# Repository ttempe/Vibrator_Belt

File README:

Vibrator Belt. 
Copyright 2016, Thomas TEMPE

The purpose of this project is to build a (physical) vibrating belt as
a tool for sensory augmentation.  The belt is fitted with coin
vibrators along its length. The one that points north vibrates at all
time.  Use it continuously for 6 weeks, and you will grow a sense of
direction. Take it off, and you will experience amputation.

For more background (and an award-winning product that you can
actually buy), see http://www.feelspace.de/navibelt/

Directory contents:
Leather belt/		DXF files for manufacturing the flexible part 
			of the belt (fabric, foam, steel band...)
			Can be edited with LibreCAD.
Belt buckle/		Fusion360 model of the buckle (for aluminium 
     			machining or 3D printing)
Vibrator_Leather_Belt/	Kicad files for making the flexible electronic 
			circuit (along the length of the belt)
Vibrator_Leather_Belt_Control_Box/  Kicd files for making the PCB 
			circuit that fits in the buckle.
Photos/			Photos of prototypes.
Code/			Arduino code for the microcontroller.
Arduino/		Arduino hardware support for the microcontroller.

The control board uses an ATMega32u4 at 8MHz.
To get it running:
* Install the Arduino IDE from Arduino.cc. Run it once, then quit it.
* Copy Arduino/*/ into your Documents/Arduino directory
* solder an 8MHz external oscillator on the back of the control board
* Start the Arduino IDE. Select Tools->Board: -> Atmega32u4 on a breadboard (8MHz internal clock)
* Connect the ISP connector to an ISP programmer. Select the proper port in Tools->Port
* Click Tools->burn bootloader
* remove the external oscillator
* Tools->Board:->LilyPad Arduino USB
* File->Examples->01. Basics->Blink
* Click « Upload » on the icon bar. The « Signal » LED should blink with 0.5Hz frequency.
* open code/Compass_band5_leather/compass_band5_leather.ino in Arduino
* Click the « upload » icon on the icon bar. control code should be uploading.

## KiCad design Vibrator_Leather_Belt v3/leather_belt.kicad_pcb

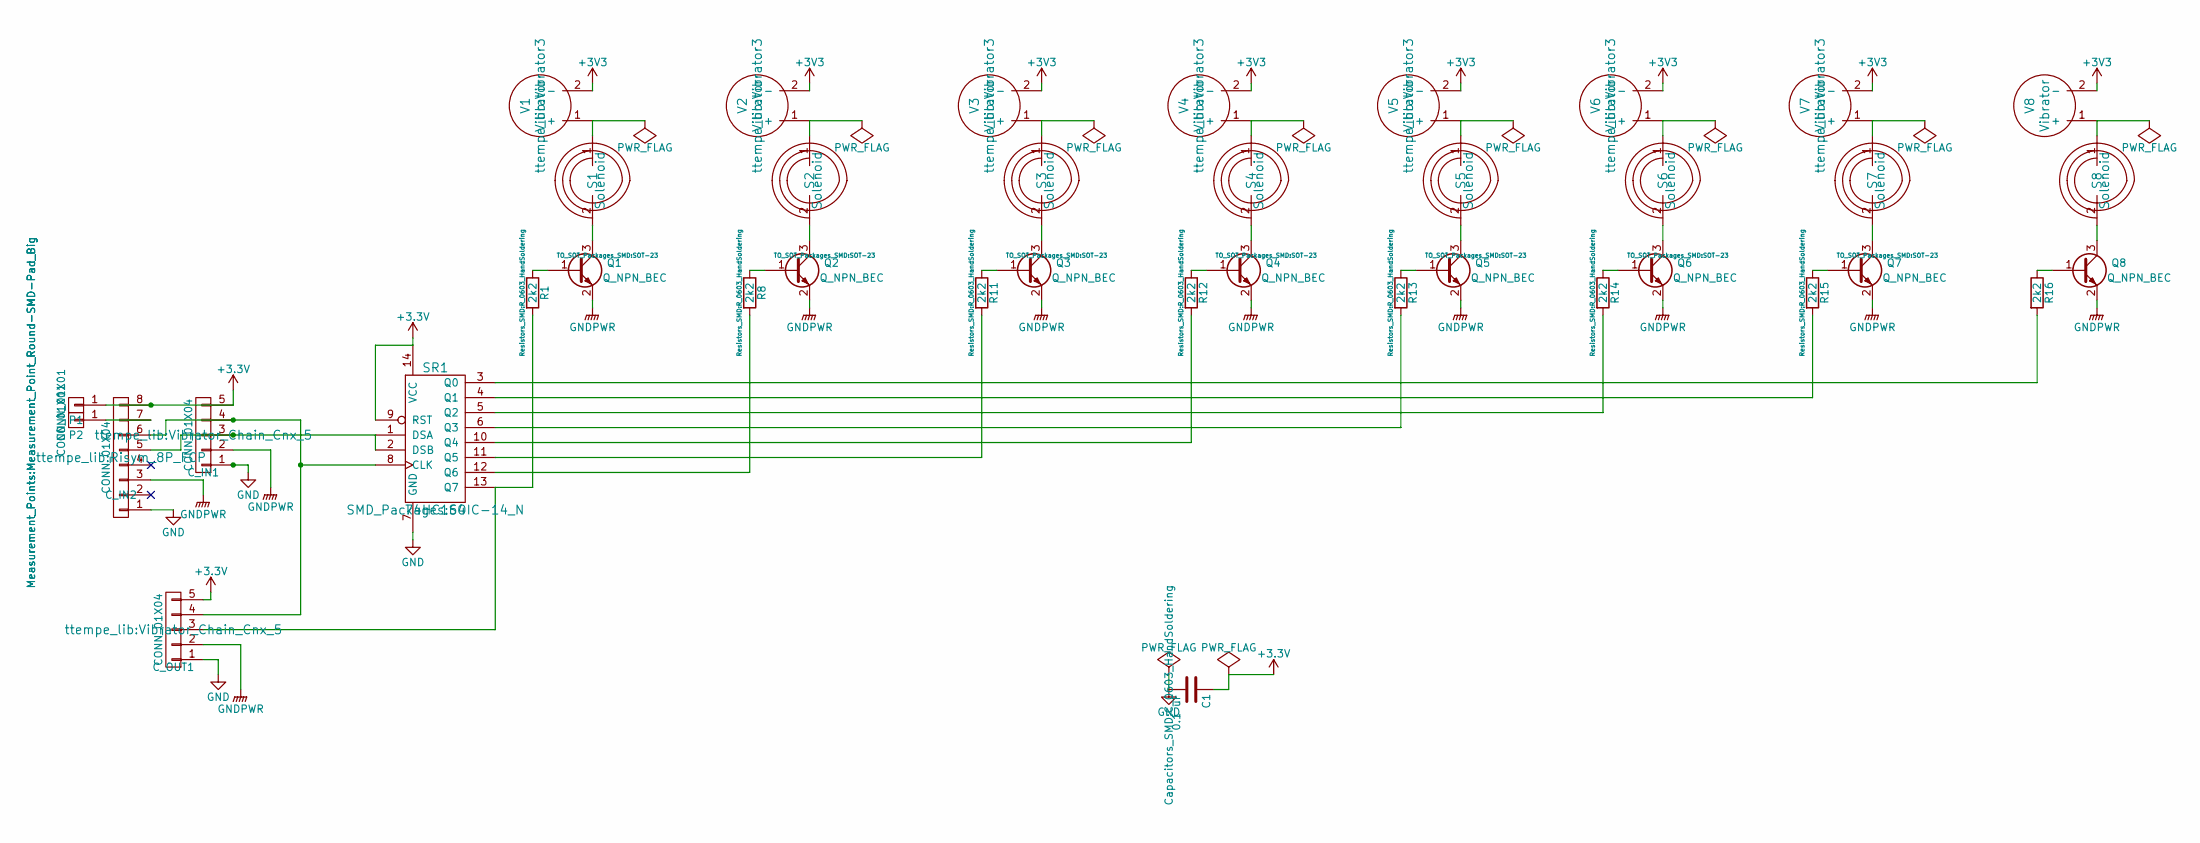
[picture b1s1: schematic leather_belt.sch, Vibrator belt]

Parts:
C1: 0.1 uF; C_0603_HandSoldering
C_IN1: CONN_01X04; Vibrator_Chain_Cnx_5
C_IN2: CONN_01X04; Risym_8P_FCP
C_OUT1: CONN_01X04; Vibrator_Chain_Cnx_5
P1, P2: CONN_01X01; Measurement_Point_Round-SMD-Pad_Big
Q1, Q2, Q3, Q4, Q5, Q6, Q7, Q8: Q_NPN_BEC; SOT-23
R1, R8, R11, R12, R13, R14, R15, R16: 2k2; R_0603_HandSoldering
S1, S2, S3, S4, S5, S6, S7, S8: Solenoid; Vibrator_antenna2
SR1: 74HC164; SOIC-14_N
V1, V2, V3, V4, V5, V6, V7, V8: Vibrator; Vibrator3

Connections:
GND: C1.2, C_IN1.1, C_IN2.1, C_OUT1.1, SR1.7 (GND)
GNDPWR: C_IN1.2, C_IN2.3, C_OUT1.2, Q1.2 (E), Q2.2 (E), Q3.2 (E), Q4.2 (E), Q5.2 (E), Q6.2 (E), Q7.2 (E), Q8.2 (E)
unnamed: C_IN1.3, C_IN2.5, SR1.1 (DSA), SR1.2 (DSB)
unnamed: C_IN1.4, C_IN2.6, C_OUT1.4, SR1.8 (CLK)
unnamed: C_IN2.7, P2.1
unnamed: C_OUT1.3, R1.2, SR1.13 (Q7)
unnamed: Q1.1 (B), R1.1
unnamed: Q1.3 (C), S1.2
unnamed: Q2.1 (B), R8.1
unnamed: Q2.3 (C), S2.2
unnamed: Q3.1 (B), R11.1
unnamed: Q3.3 (C), S3.2
unnamed: Q4.1 (B), R12.1
unnamed: Q4.3 (C), S4.2
unnamed: Q5.1 (B), R13.1
unnamed: Q5.3 (C), S5.2
unnamed: Q6.1 (B), R14.1
unnamed: Q6.3 (C), S6.2
unnamed: Q7.1 (B), R15.1
unnamed: Q7.3 (C), S7.2
unnamed: Q8.1 (B), R16.1
unnamed: Q8.3 (C), S8.2
unnamed: R8.2, SR1.12 (Q6)
unnamed: R11.2, SR1.11 (Q5)
unnamed: R12.2, SR1.10 (Q4)
unnamed: R13.2, SR1.6 (Q3)
unnamed: R14.2, SR1.5 (Q2)
unnamed: R15.2, SR1.4 (Q1)
unnamed: R16.2, SR1.3 (Q0)
unnamed: S1.1, V1.1 (+)
unnamed: S2.1, V2.1 (+)
unnamed: S3.1, V3.1 (+)
unnamed: S4.1, V4.1 (+)
unnamed: S5.1, V5.1 (+)
unnamed: S6.1, V6.1 (+)
unnamed: S7.1, V7.1 (+)
unnamed: S8.1, V8.1 (+)

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
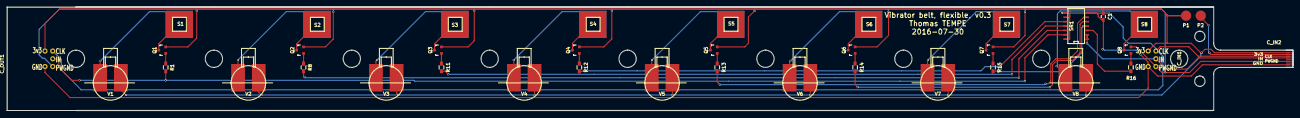
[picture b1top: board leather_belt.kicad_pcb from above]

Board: 2 copper layers, 373.0 x 30.0 mm, 39 parts (0 on the bottom side), 38 nets.

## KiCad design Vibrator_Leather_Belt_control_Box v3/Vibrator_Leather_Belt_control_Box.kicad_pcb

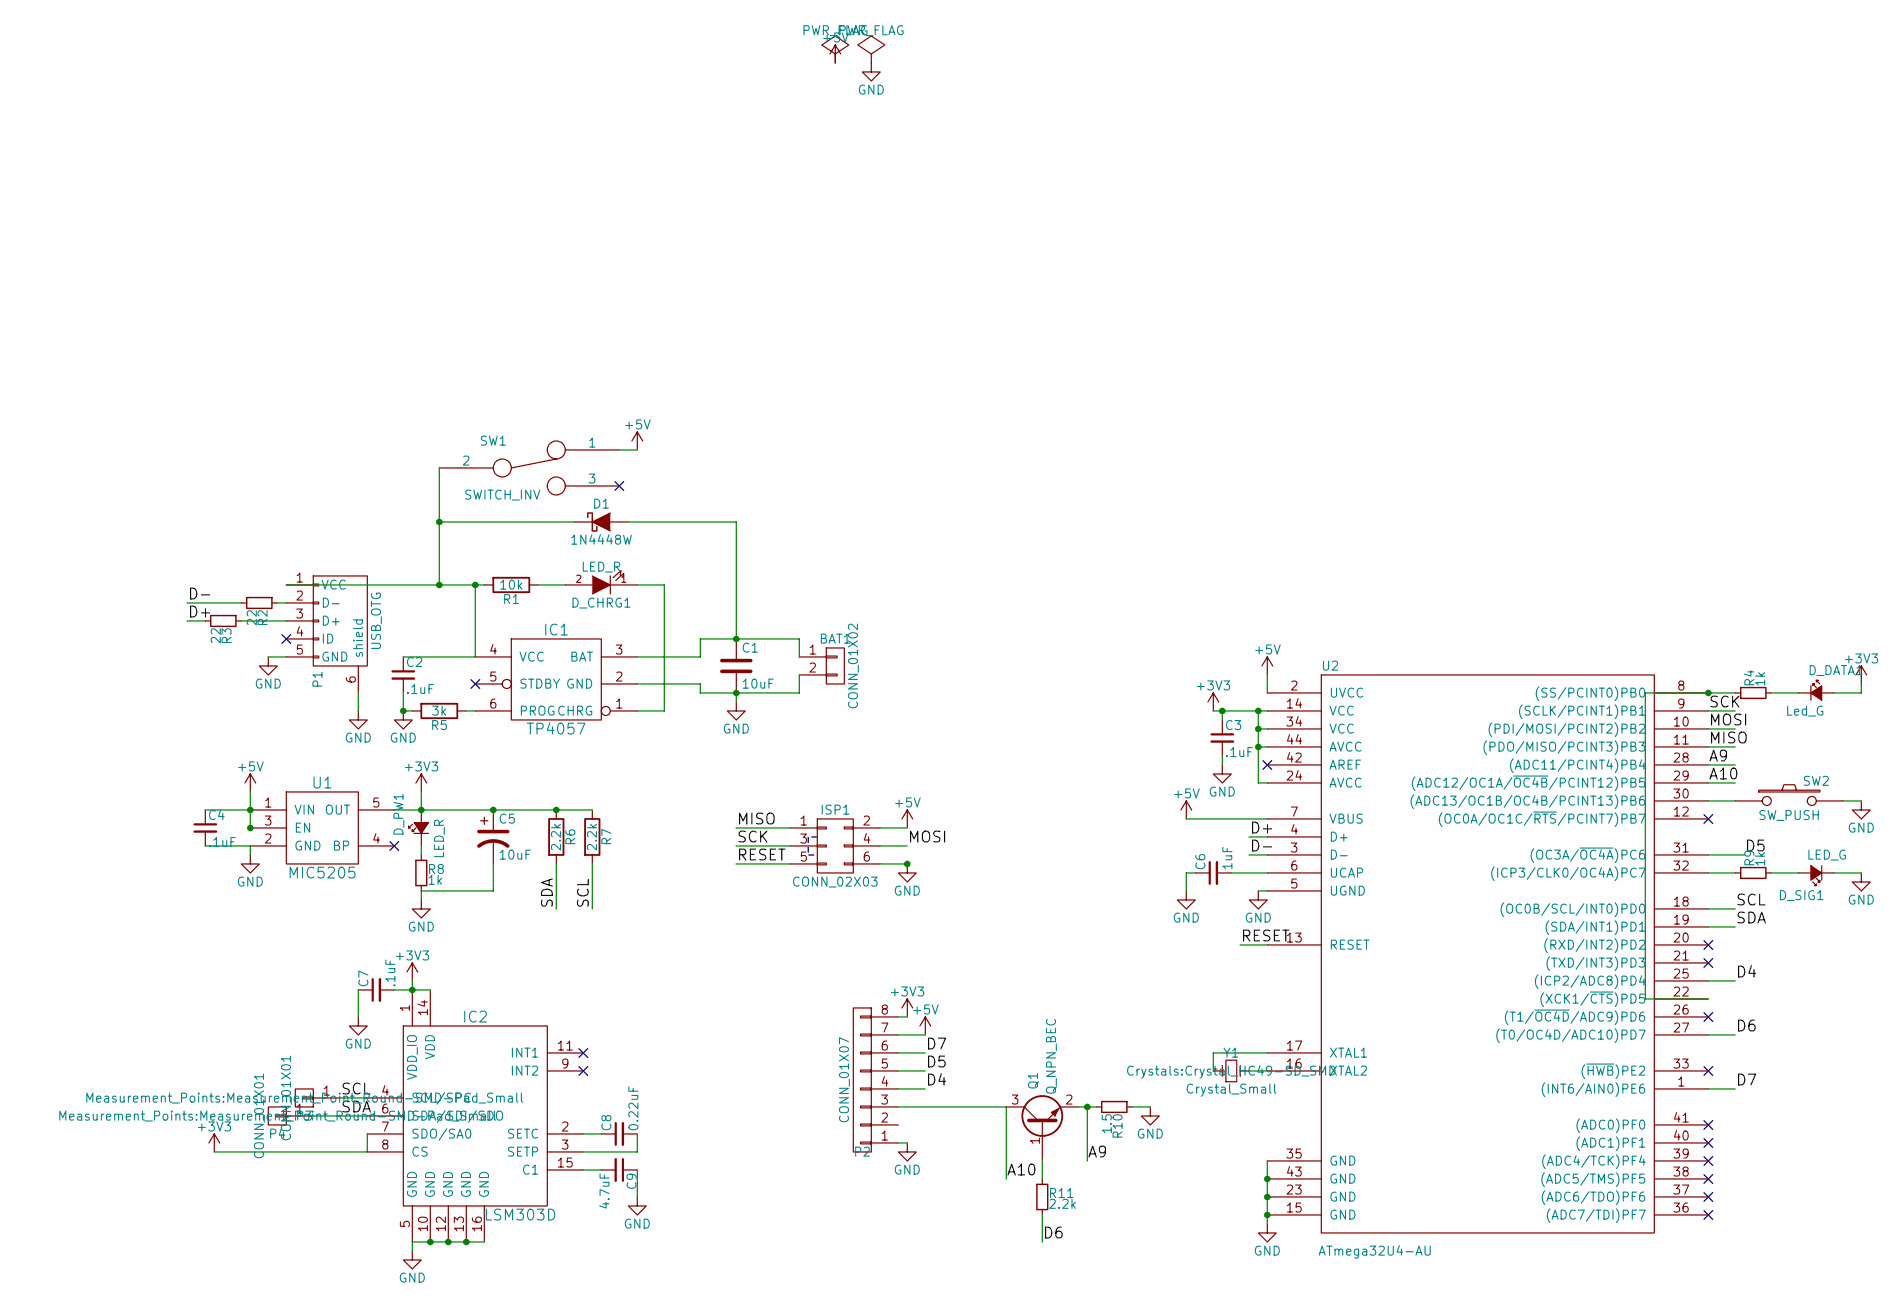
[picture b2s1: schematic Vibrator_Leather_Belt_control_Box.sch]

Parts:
BAT1: CONN_01X02; Conn_1x2_2mm
C1, C5: 10uF; R_0805_HandSoldering
C2, C3, C4, C7: .1uF; R_0603_HandSoldering
C6: 1uF; R_0603_HandSoldering
C8: 0.22uF; R_0603_HandSoldering
C9: 4.7uF; R_0603_HandSoldering
D1: 1N4448W; SOD-123
D_CHRG1: LED_R; LED_1206_reversed
D_DATA1: Led_G; LED_1206_reversed
D_PW1: LED_R; LED_1206_reversed
D_SIG1: LED_G; LED_1206_reversed
IC1: TP4057; SOT-23-6
IC2: LSM303D; TFLGA-3.0x3.0x1.0_16L
ISP1: CONN_02X03; Pin_Header_Straight_2x03
P1: USB_OTG; Micro_USB_MK5P
P2: CONN_01X07; Risym_8P_SMD
P3, P4: CONN_01X01; Measurement_Point_Round-SMD-Pad_Small
Q1: Q_NPN_BEC; SOT-23_Handsoldering
R1: 10k; R_0603_HandSoldering
R2, R3: 22; R_0603_HandSoldering
R4, R8, R9: 1k; R_0603_HandSoldering
R5: 3k; R_0603_HandSoldering
R6, R7, R11: 2.2k; R_0603_HandSoldering
R10: 1.5; R_0603_HandSoldering
SW1: SWITCH_INV; SMD_side_switch_MSK-12C01-07
SW2: SW_PUSH; SMD_side_push_button_2x4x3.5
U1: MIC5205; SOT-23-5
U2: ATmega32U4-AU; TQFP-44_10x10mm_Pitch0.8mm
Y1: Crystal_Small; Crystal_HC49-SD_SMD

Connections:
+3V3: C3.1, C5.1, C7.2, D_DATA1.2 (A), D_PW1.2 (A), IC2.1 (VDD_IO), IC2.7 (SDO/SA0), IC2.8 (CS), IC2.14 (VDD), P2.8, R6.1, R7.1, U1.5 (OUT), U2.14 (VCC), U2.24 (AVCC), U2.34 (VCC), U2.44 (AVCC)
+5V: C4.1, ISP1.2, P2.7, SW1.1, U1.1 (VIN), U1.3 (EN), U2.2 (UVCC), U2.7 (VBUS)
/A9: Q1.2 (E), R10.2, U2.28 ((ADC11/PCINT4)PB4)
/A10: P2.3, Q1.3 (C), U2.29 ((ADC12/OC1A/~OC4B~/PCINT12)PB5)
/D4: P2.4, U2.25 ((ICP2/ADC8)PD4)
/D5: P2.5, U2.31 ((OC3A/~OC4A~)PC6)
/D6: R11.2, U2.27 ((T0/OC4D/ADC10)PD7)
/D7: P2.6, U2.1 ((INT6/AIN0)PE6)
/D+: R3.2, U2.4 (D+)
/D-: R2.2, U2.3 (D-)
/MISO: ISP1.1, U2.11 ((PDO/MISO/PCINT3)PB3)
/MOSI: ISP1.4, U2.10 ((PDI/MOSI/PCINT2)PB2)
/RESET: ISP1.5, U2.13 (RESET)
/SCK: ISP1.3, U2.9 ((SCLK/PCINT1)PB1)
/SCL: IC2.4 (SCL/SPC), P3.1, R7.2, U2.18 ((OC0B/SCL/INT0)PD0)
/SDA: IC2.6 (SDA/SDI/SDO), P4.1, R6.2, U2.19 ((SDA/INT1)PD1)
GND: BAT1.2, C1.2, C2.2, C3.2, C4.2, C5.2, C6.1, C7.1, C9.1, D_SIG1.1 (K), IC1.2 (GND), IC2.5 (GND), IC2.10 (GND), IC2.12 (GND), IC2.13 (GND), IC2.16 (GND), ISP1.6, P1.5 (GND), P1.6 (shield), P2.1, R5.2, R8.2, R10.1, SW2.2, U1.2 (GND), U2.5 (UGND), U2.15 (GND), U2.23 (GND), U2.35 (GND), U2.43 (GND)
unnamed: BAT1.1, C1.1, D1.2 (A), IC1.3 (BAT)
unnamed: C2.1, D1.1 (K), IC1.4 (VCC), P1.1 (VCC), R1.2, SW1.2
unnamed: C6.2, U2.6 (UCAP)
unnamed: C8.1, IC2.2 (SETC)
unnamed: C8.2, IC2.3 (SETP)
unnamed: C9.2, IC2.15 (C1)
unnamed: D_CHRG1.1 (K), IC1.1 (CHRG)
unnamed: D_CHRG1.2 (A), R1.1
unnamed: D_DATA1.1 (K), R4.2
unnamed: D_PW1.1 (K), R8.1
unnamed: D_SIG1.2 (A), R9.2
unnamed: IC1.6 (PROG), R5.1
unnamed: P1.2 (D-), R2.1
unnamed: P1.3 (D+), R3.1
unnamed: Q1.1 (B), R11.1
unnamed: R4.1, U2.8 ((SS/PCINT0)PB0), U2.22 ((XCK1/~CTS~)PD5)
unnamed: R9.1, U2.32 ((ICP3/CLK0/OC4A)PC7)
unnamed: SW2.1, U2.30 ((ADC13/OC1B/OC4B/PCINT13)PB6)
unnamed: U2.16 (XTAL2), Y1.2
unnamed: U2.17 (XTAL1), Y1.1

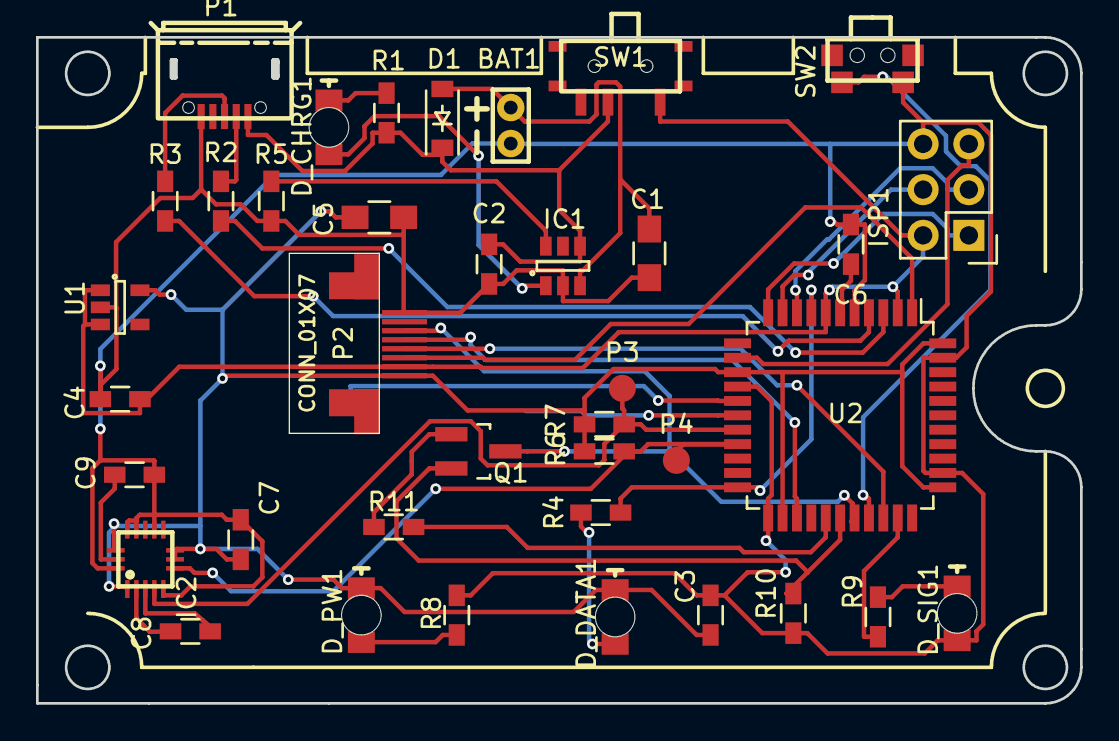
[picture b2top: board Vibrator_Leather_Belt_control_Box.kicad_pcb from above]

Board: 2 copper layers, 57.9 x 36.9 mm, 39 parts (1 on the bottom side), 37 nets.

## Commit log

2016-12-01 More details. Feelspace link.
